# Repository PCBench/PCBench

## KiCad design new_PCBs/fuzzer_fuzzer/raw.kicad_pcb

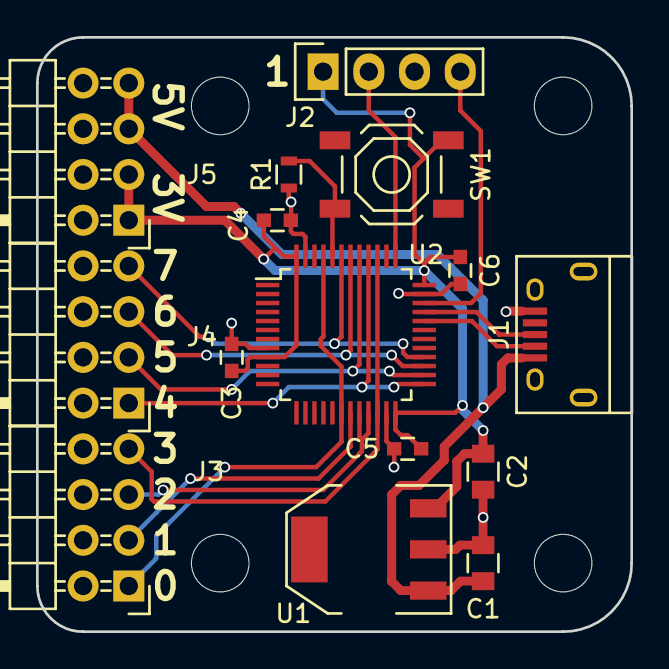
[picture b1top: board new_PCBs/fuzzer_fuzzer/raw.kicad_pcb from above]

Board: 2 copper layers, 33.0 x 33.0 mm, 15 parts (0 on the bottom side), 16 nets.

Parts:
C1, C2: 1u; C_0805
C3, C4, C5, C6: 100n; C_0603
J1: USB_OTG; USB_Micro-B
J2: CONN_01X04; Pin_Header_Straight_1x04
J3, J4, J5: CONN_02X04; Pin_Header_Angled_2x04
R1: 10K; R_0603
SW1: SPST; SW_SPST_TL3342
U1: SOT223-REG; SOT-223
U2: STM32F042-48; LQFP-48_7x7mm_Pitch0.5mm

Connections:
+5V: C1.1, J1.1, J5.5, J5.7, U1.1
/BOOT: R1.1, SW1.1, U2.44
/D0: J3.1, U2.18, U2.45
/D1: J3.3, U2.19
/D2: J3.5, U2.20, U2.21
/D3: J3.7, U2.22, U2.39
/D4: J4.1, U2.25, U2.40
/D5: J4.3, U2.26, U2.41
/D6: J4.5, U2.27, U2.42
/D7: J4.7, U2.28, U2.43
/SWCLK: J2.2, U2.37
/SWDAT: J2.4, U2.34
/USB_DM: J1.2, U2.32
/USB_DP: J1.3, U2.33
GND: C1.2, C2.2, C3.2, C4.2, C5.2, C6.2, J1.5, J2.3, J3.2, J3.4, J3.6, J3.8, J4.2, J4.4, J4.6, J4.8, J5.2, J5.4, J5.6, J5.8, R1.2, U1.2, U1.4, U2.8, U2.23, U2.35, U2.47
VDD: C2.1, C3.1, C4.1, C5.1, C6.1, J2.1, J5.1, J5.3, SW1.2, U1.3, U2.9, U2.24, U2.36, U2.48

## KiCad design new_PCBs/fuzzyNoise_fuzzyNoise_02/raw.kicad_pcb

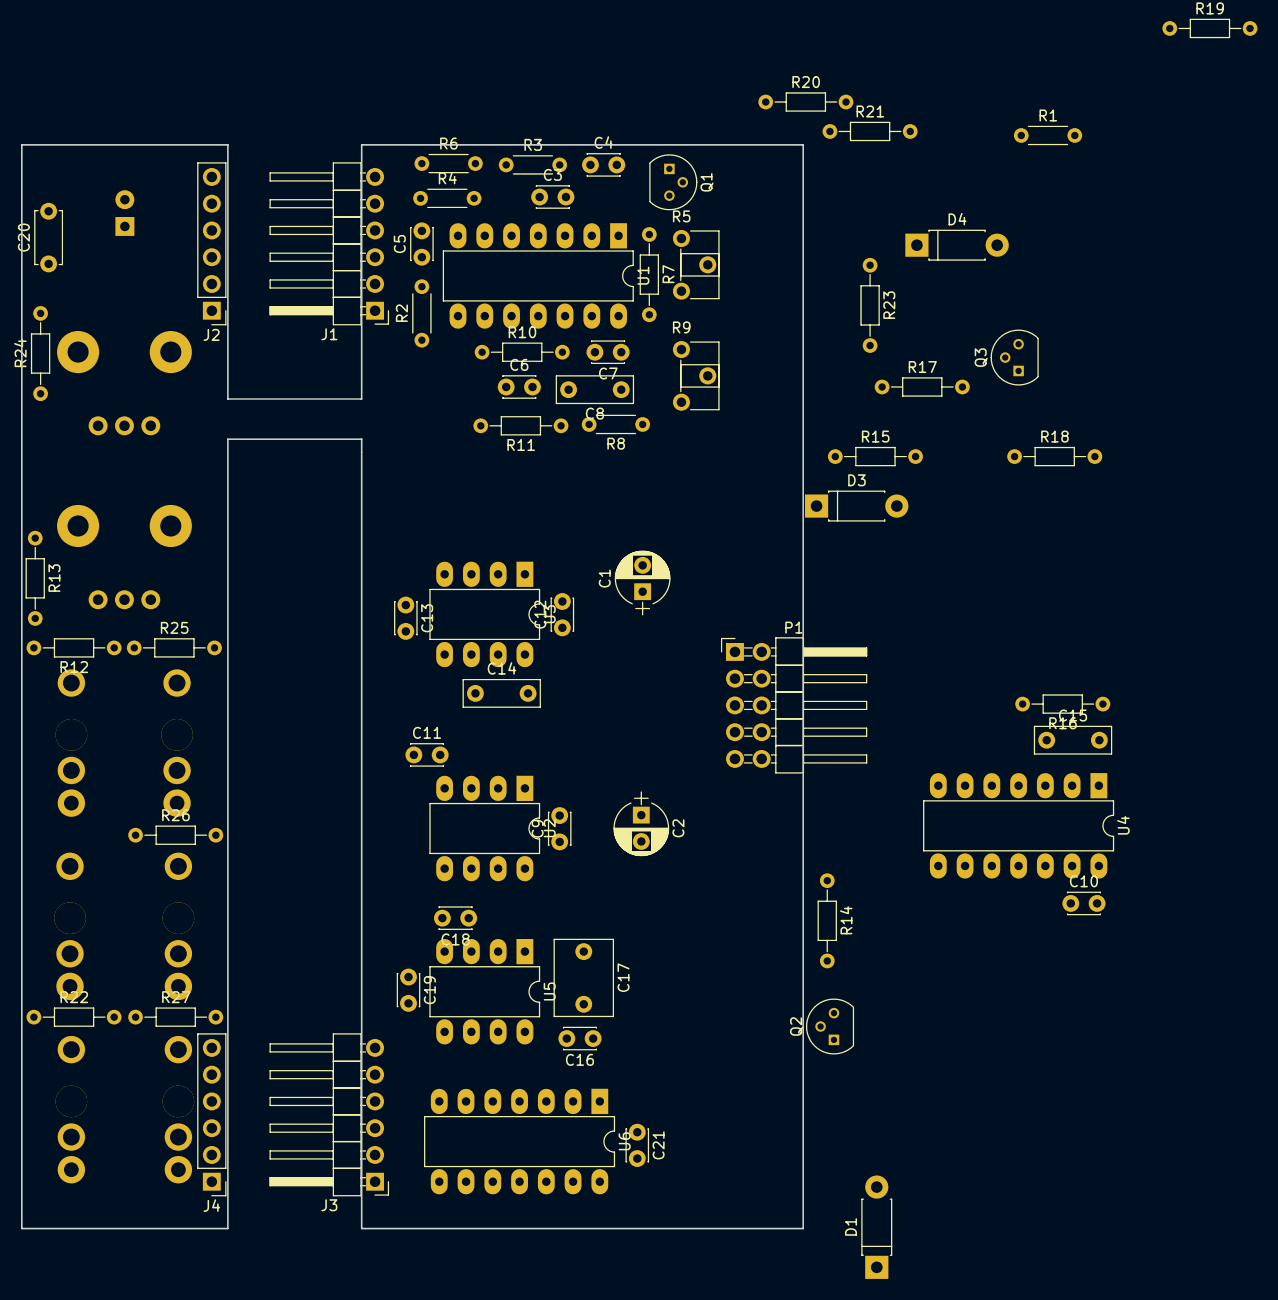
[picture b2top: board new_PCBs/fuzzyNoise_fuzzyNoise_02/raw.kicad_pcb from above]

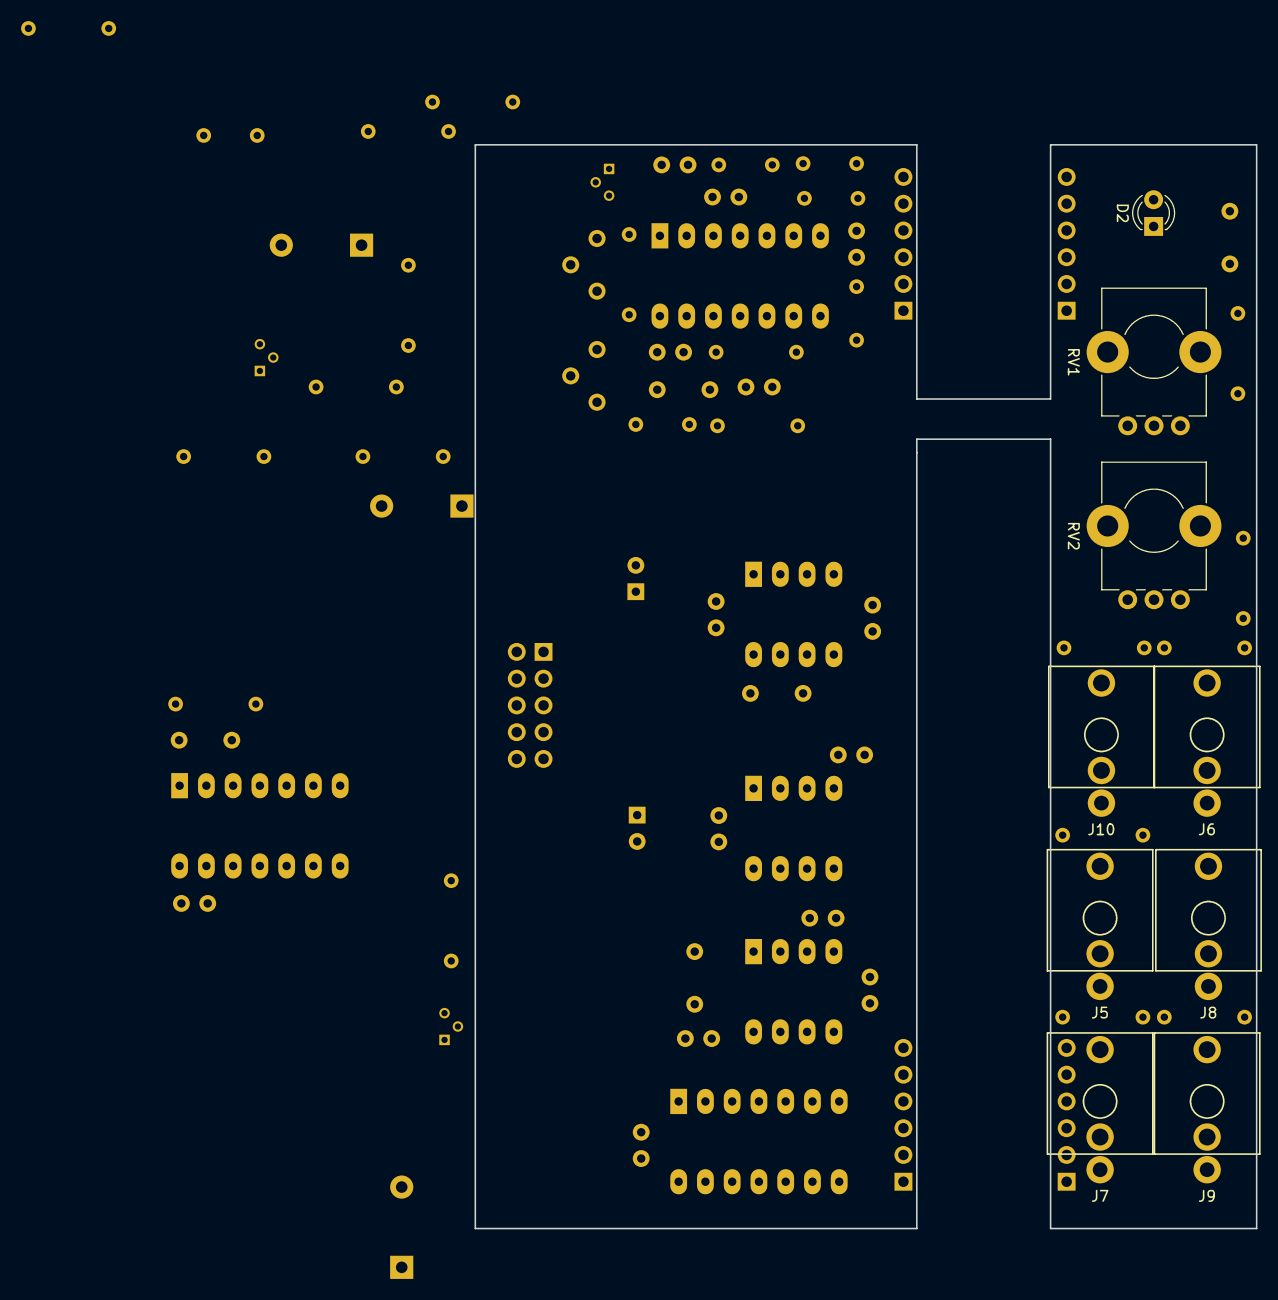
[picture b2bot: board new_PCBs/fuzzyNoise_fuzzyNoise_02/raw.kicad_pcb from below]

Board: 2 copper layers, 74.2 x 102.9 mm, 74 parts (9 on the bottom side), 58 nets, no tracks yet.

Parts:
C1, C2: 10uF; CP_Radial_D5.0mm_P2.50mm
C3, C5, C6, C9, C10, C11, C12, C13, C16, C18, C19, C21: 100nF; C_Disc_D3.0mm_W2.0mm_P2.50mm
C4: 220nF; C_Disc_D3.0mm_W2.0mm_P2.50mm
C7: 1nF; C_Disc_D3.0mm_W2.0mm_P2.50mm
C8: 10nF; C_Rect_L7.2mm_W2.5mm_P5.00mm_FKS2_FKP2_MKS2_MKP2
C14: 2n2 polybox; C_Rect_L7.2mm_W2.5mm_P5.00mm_FKS2_FKP2_MKS2_MKP2
C15: 1nF; C_Rect_L7.2mm_W2.5mm_P5.00mm_FKS2_FKP2_MKS2_MKP2
C17: 1uF; C_Rect_L7.2mm_W5.5mm_P5.00mm_FKS2_FKP2_MKS2_MKP2
C20: 470nF; C_Disc_D5.0mm_W2.5mm_P5.00mm
D1, D3, D4: 1N4148; D_DO-41_SOD81_P7.62mm_Horizontal
D2: LED; LED_D3.0mm
J1: mainTop; Pin_Header_Angled_1x06_Pitch2.54mm
J2: panelTop; Socket_Strip_Straight_1x06_Pitch2.54mm
J3: mainBase; Pin_Header_Angled_1x06_Pitch2.54mm
J4: panelBase; Socket_Strip_Straight_1x06_Pitch2.54mm
J5: whiteOut; Thonkiconn
J6: signalIn; Thonkiconn
J7: pinkOut; Thonkiconn
J8: gateIn; Thonkiconn
J9: LFOout; Thonkiconn
J10: CVout; Thonkiconn
P1: PWR_IN_02x05_conn; Pin_Header_Angled_2x05_Pitch2.54mm
Q1, Q2, Q3: 2N3904; TO-92_Molded_Narrow
R1: 1M; R_Axial_DIN0204_L3.6mm_D1.6mm_P5.08mm_Horizontal
R2, R4, R8: 10K; R_Axial_DIN0204_L3.6mm_D1.6mm_P5.08mm_Horizontal
R3: 2M2; R_Axial_DIN0204_L3.6mm_D1.6mm_P5.08mm_Horizontal
R5: 500K trim; Potentiometer_Trimmer_ACP_CA6h_Vertical
R6: 470K; R_Axial_DIN0204_L3.6mm_D1.6mm_P5.08mm_Horizontal
R7, R13, R18, R19, R20: 100K; R_Axial_DIN0204_L3.6mm_D1.6mm_P7.62mm_Horizontal
R9: 100K trim; Potentiometer_Trimmer_ACP_CA6h_Vertical
R10: 47K; R_Axial_DIN0204_L3.6mm_D1.6mm_P7.62mm_Horizontal
R11: 270K; R_Axial_DIN0204_L3.6mm_D1.6mm_P7.62mm_Horizontal
R12, R22, R24, R25, R26, R27: 1K; R_Axial_DIN0204_L3.6mm_D1.6mm_P7.62mm_Horizontal
R14, R23: 10K; R_Axial_DIN0204_L3.6mm_D1.6mm_P7.62mm_Horizontal
R15: 1M; R_Axial_DIN0204_L3.6mm_D1.6mm_P7.62mm_Horizontal
R16: 1K5; R_Axial_DIN0204_L3.6mm_D1.6mm_P7.62mm_Horizontal
R17: 2K; R_Axial_DIN0204_L3.6mm_D1.6mm_P7.62mm_Horizontal
R21: 22K; R_Axial_DIN0204_L3.6mm_D1.6mm_P7.62mm_Horizontal
RV1: 1M lin; Potentiometer_Alps_RK09K_Horizontal
RV2: 470K lin; Potentiometer_Alps_RK09K_Horizontal
U1, U6: TL074; DIP-14_W7.62mm_LongPads
U2, U5: TL072; DIP-8_W7.62mm_LongPads
U3: LF398; DIP-8_W7.62mm_LongPads
U4: 4047; DIP-14_W7.62mm_LongPads

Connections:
/LFO/CV_out: J3.6, U6.6, U6.7
/LFO/LFO_out: J3.1, U6.1, U6.2
/LFO/from_glide_pot: J1.2, U6.5
/LFO/from_rate_pot: J1.4, R20.1, R21.2, U5.7
/LFO/pinkNoise_out_preBuffer: R9.1, U1.8, U6.12
/LFO/pink_noise_out: J3.2, U6.13, U6.14
/LFO/to_LED: J1.6, Q3.1
/LFO/to_rate_pot: C17.1, J1.5, U5.6
/LFO/whiteNoise_out_preBuffer: R5.1, R7.1, U1.1, U6.10
/LFO/white_noise_out: J3.4, U6.8, U6.9
/panel/CV_out: J4.6, R25.2
/panel/LFO_out: J4.1, R22.2
/panel/from_glide_pot: C20.1, J2.2, RV2.1
/panel/from_rate_pot: J2.4, RV1.1, RV1.2
/panel/gate_input: J4.3, J8.3
/panel/ground: C20.2, D2.1, J2.1, J5.1, J6.1, J7.1, J8.1, J9.1, J10.1, R13.2
/panel/pink_noise_out: J4.2, R27.2
/panel/signal_in: J4.5, R12.1, R13.1
/panel/to_LED: D2.2, J2.6
/panel/to_glide_pot: J2.3, RV2.2, RV2.3
/panel/to_rate_pot: J2.5, R24.2
/panel/white_noise_out: J4.4, R26.2
/sampleAndHold/gate_input: D1.1, J3.3, Q2.2, R15.1
/sampleAndHold/signal_in: J3.5, U2.3
/sampleAndHold/to_glide_pot: J1.3, U2.6, U2.7
GND: C1.2, C2.1, C3.2, C6.1, C9.1, C10.1, C11.1, C12.1, C13.2, C14.2, C16.1, C17.2, C18.1, C19.1, C21.1, D1.2, J1.1, P1.3, P1.4, P1.5, P1.6, P1.7, P1.8, Q2.1, R3.2, R4.2, R15.2, R19.2, U1.3, U1.10, U1.12, U3.7, U4.5, U4.7, U4.9, U4.12, U5.3
unnamed: C4.1, R3.1, U1.5
unnamed: C4.2, Q1.1, R1.2
unnamed: C5.1, R2.2
unnamed: C5.2, R6.1, U1.7
unnamed: C7.1, C8.1, R8.2, R11.1, U1.14
unnamed: C7.2, R7.2, R10.2, R11.2, U1.13
unnamed: C8.2, R10.1
unnamed: C14.1, U3.6
unnamed: C15.1, R16.2, U4.3
unnamed: C15.2, U4.1
unnamed: D3.1, R18.2, R23.1, U6.3
unnamed: D3.2, D4.1, U5.1
unnamed: D4.2, R21.1, R23.2, U5.2
unnamed: J5.3, J6.2, R26.1
unnamed: J6.3, R12.2
unnamed: J7.3, R27.1
unnamed: J8.2, J9.3, R22.1
unnamed: J10.3, R25.1
unnamed: Q2.3, R14.2, U4.6
unnamed: Q3.2, R18.1
unnamed: Q3.3, R17.1
unnamed: R2.1, R5.2, U1.2
unnamed: R4.1, R6.2, U1.6
unnamed: R8.1, R9.2, U1.9
unnamed: R16.1, U4.2
unnamed: R19.1, R20.2, U5.5
unnamed: R24.1, RV1.3
unnamed: U2.1, U2.2, U3.3
unnamed: U2.5, U3.5
unnamed: U3.8, U4.10
VCC: C1.1, C3.1, C9.2, C10.2, C12.2, C16.2, C19.2, P1.1, P1.2, R1.1, R14.1, R17.2, U1.4, U2.8, U3.1, U4.4, U4.8, U4.14, U5.8, U6.4
VEE: C2.2, C6.2, C11.2, C13.1, C18.2, C21.2, P1.9, P1.10, Q1.2, U1.11, U2.4, U3.4, U5.4, U6.11

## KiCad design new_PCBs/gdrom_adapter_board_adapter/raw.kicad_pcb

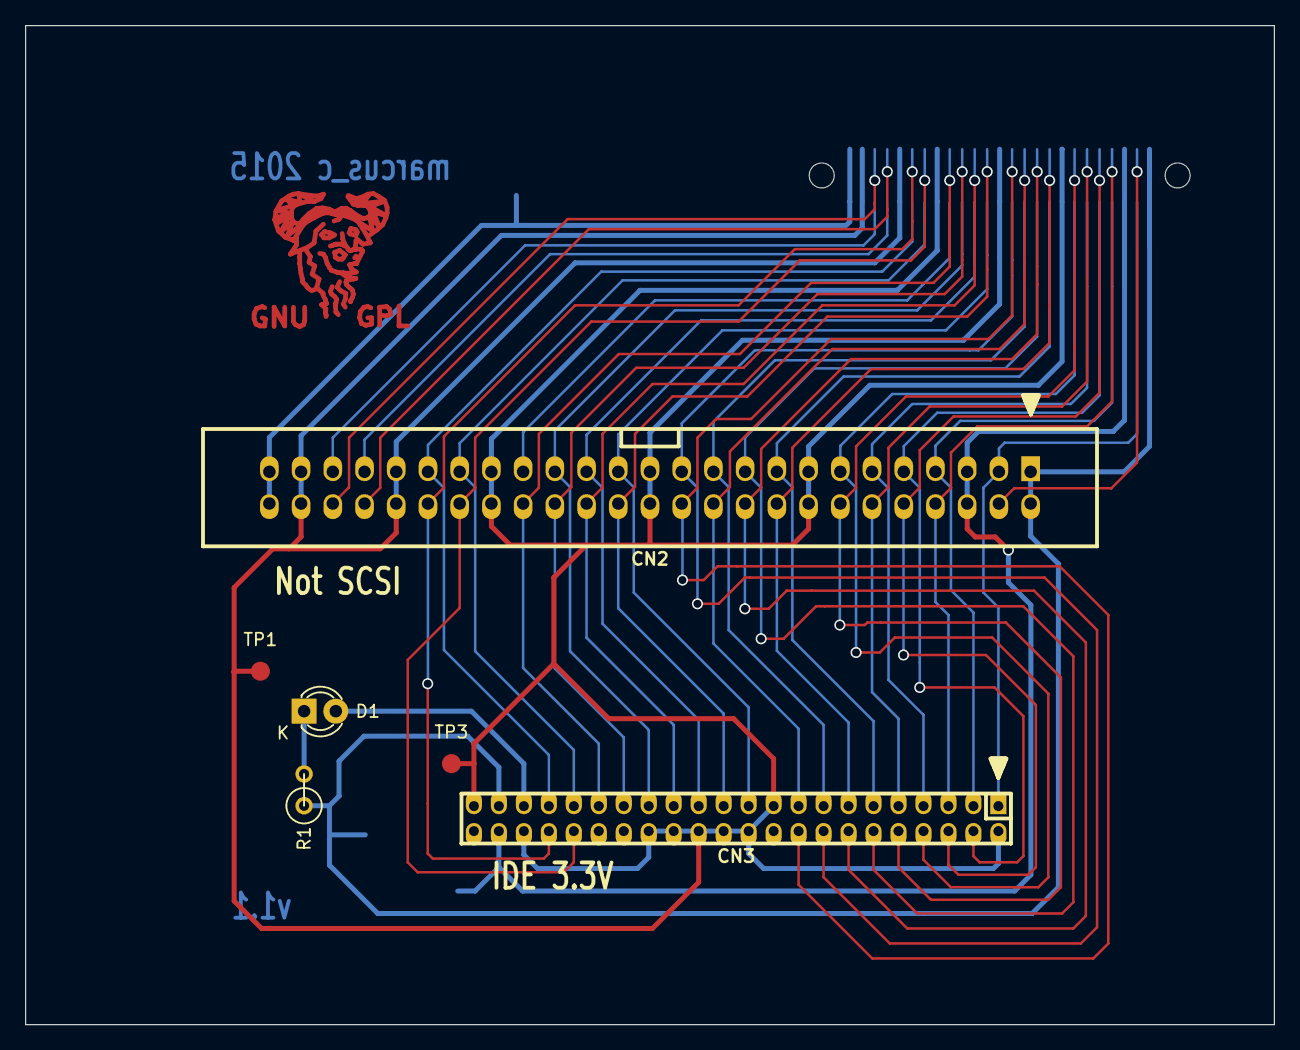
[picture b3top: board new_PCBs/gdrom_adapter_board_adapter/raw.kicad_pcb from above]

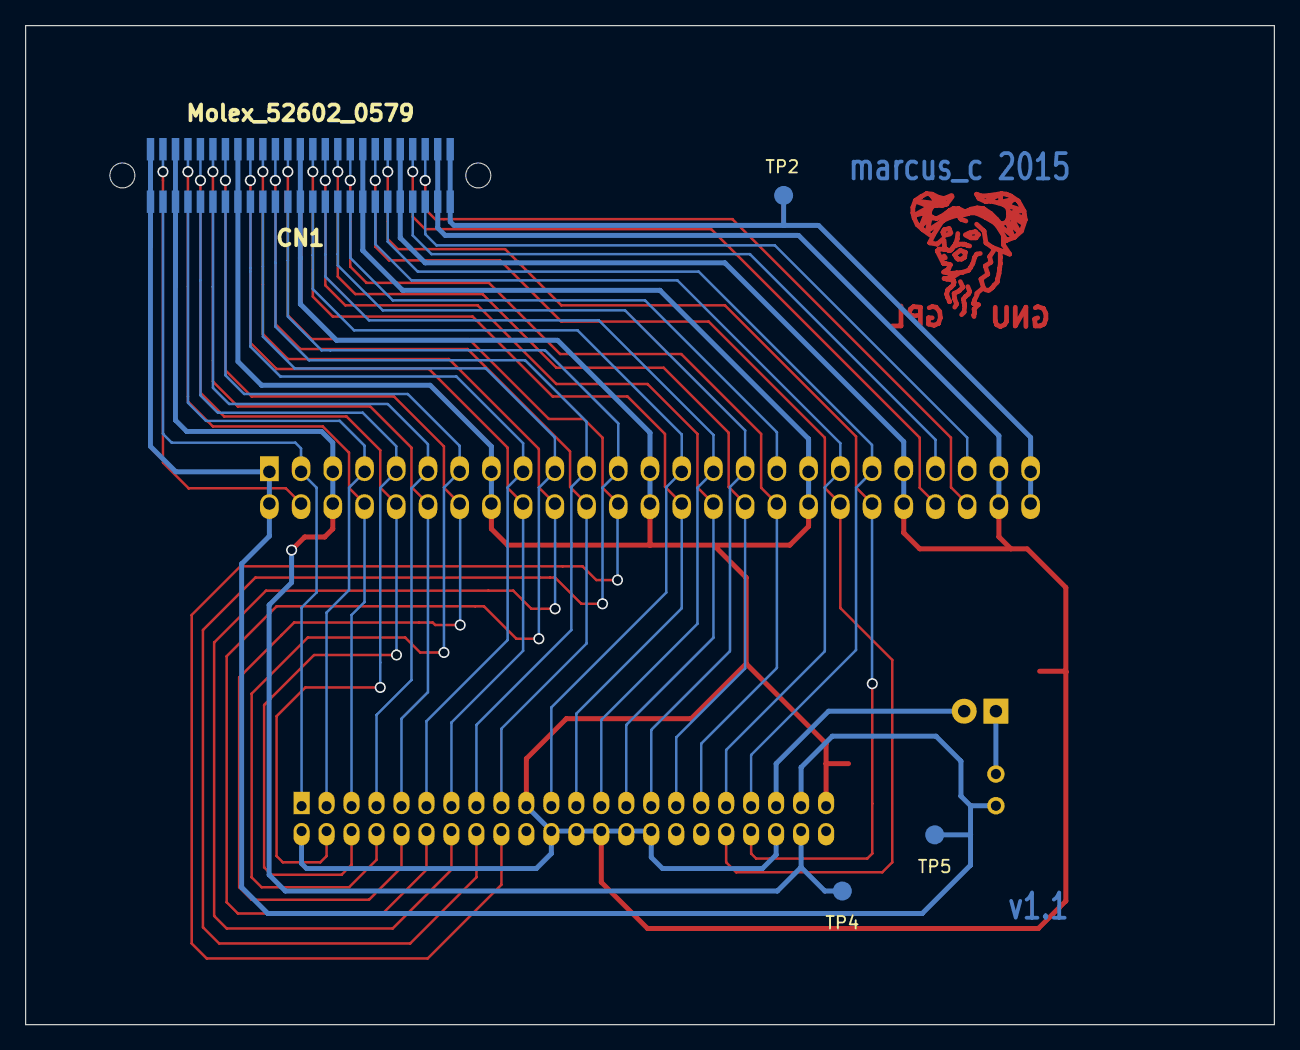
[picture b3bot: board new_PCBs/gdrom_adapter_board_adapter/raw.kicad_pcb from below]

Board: 2 copper layers, 100.0 x 80.0 mm, 10 parts (4 on the bottom side), 40 nets.

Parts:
CN1: Molex_52602_0579
CN2: CONN_25X2; vasch_strip_25x2
CN3: CONN_02X22; pin_strip_2mm_22x2
D1: LED; LED-3MM
R1: 1k; R1
TP1, TP2, TP3, TP4, TP5: Measurement_Point_Round-SMD-Pad_Small

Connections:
+3V3: CN1.A1, CN1.B1, CN2.1, CN2.2, CN3.41, R1.1, TP5.1
+5V: CN1.A3, CN1.B3, CN2.5, CN2.6, CN3.42, TP4.1
+12V: CN1.A25, CN1.B25, CN2.49, CN2.50, TP2.1
/A0: CN1.A19, CN2.37, CN3.35
/A1: CN1.B17, CN2.34, CN3.33
/A2: CN1.B19, CN2.38, CN3.36
/ACTIVEn: CN3.39, D1.2
/CD_CLK: CN1.B23, CN2.46
/CS0n: CN1.A20, CN2.39, CN3.37
/CS1n: CN1.B20, CN2.40, CN3.38
/D0: CN1.B11, CN2.22, CN3.17
/D1: CN1.A11, CN2.21, CN3.15
/D2: CN1.B9, CN2.18, CN3.13
/D3: CN1.A9, CN2.17, CN3.11
/D4: CN1.B6, CN2.12, CN3.9
/D5: CN1.A6, CN2.11, CN3.7
/D6: CN1.B4, CN2.8, CN3.5
/D7: CN1.A4, CN2.7, CN3.3
/D8: CN1.A5, CN2.9, CN3.4
/D9: CN1.B5, CN2.10, CN3.6
/D10: CN1.A7, CN2.13, CN3.8
/D11: CN1.B7, CN2.14, CN3.10
/D12: CN1.A10, CN2.19, CN3.12
/D13: CN1.B10, CN2.20, CN3.14
/D14: CN1.A12, CN2.23, CN3.16
/D15: CN1.B12, CN2.24, CN3.18
/DMACKn: CN1.A16, CN2.31, CN3.29
/DMARQ: CN1.A14, CN2.27, CN3.21
/EMPH: CN1.A17, CN2.33
/G_RST: CN1.A2, CN2.3, CN3.1
/INTRQ: CN1.B16, CN2.32, CN3.31
/IORDY: CN1.B15, CN2.30, CN3.27
/LRCK: CN1.B22, CN2.44
/RDn: CN1.A15, CN2.29, CN3.25
/SCK: CN1.A22, CN2.43
/SDAT: CN1.A23, CN2.45
/WRn: CN1.B14, CN2.28, CN3.23
/xB2: CN1.B2, CN2.4
GND: CN1.A8, CN1.A13, CN1.A18, CN1.A21, CN1.A24, CN1.B8, CN1.B13, CN1.B18, CN1.B21, CN1.B24, CN2.15, CN2.16, CN2.25, CN2.26, CN2.35, CN2.36, CN2.41, CN2.42, CN2.47, CN2.48, CN3.2, CN3.19, CN3.22, CN3.24, CN3.26, CN3.28, CN3.30, CN3.40, CN3.43, TP1.1, TP3.1
unnamed: D1.1, R1.2

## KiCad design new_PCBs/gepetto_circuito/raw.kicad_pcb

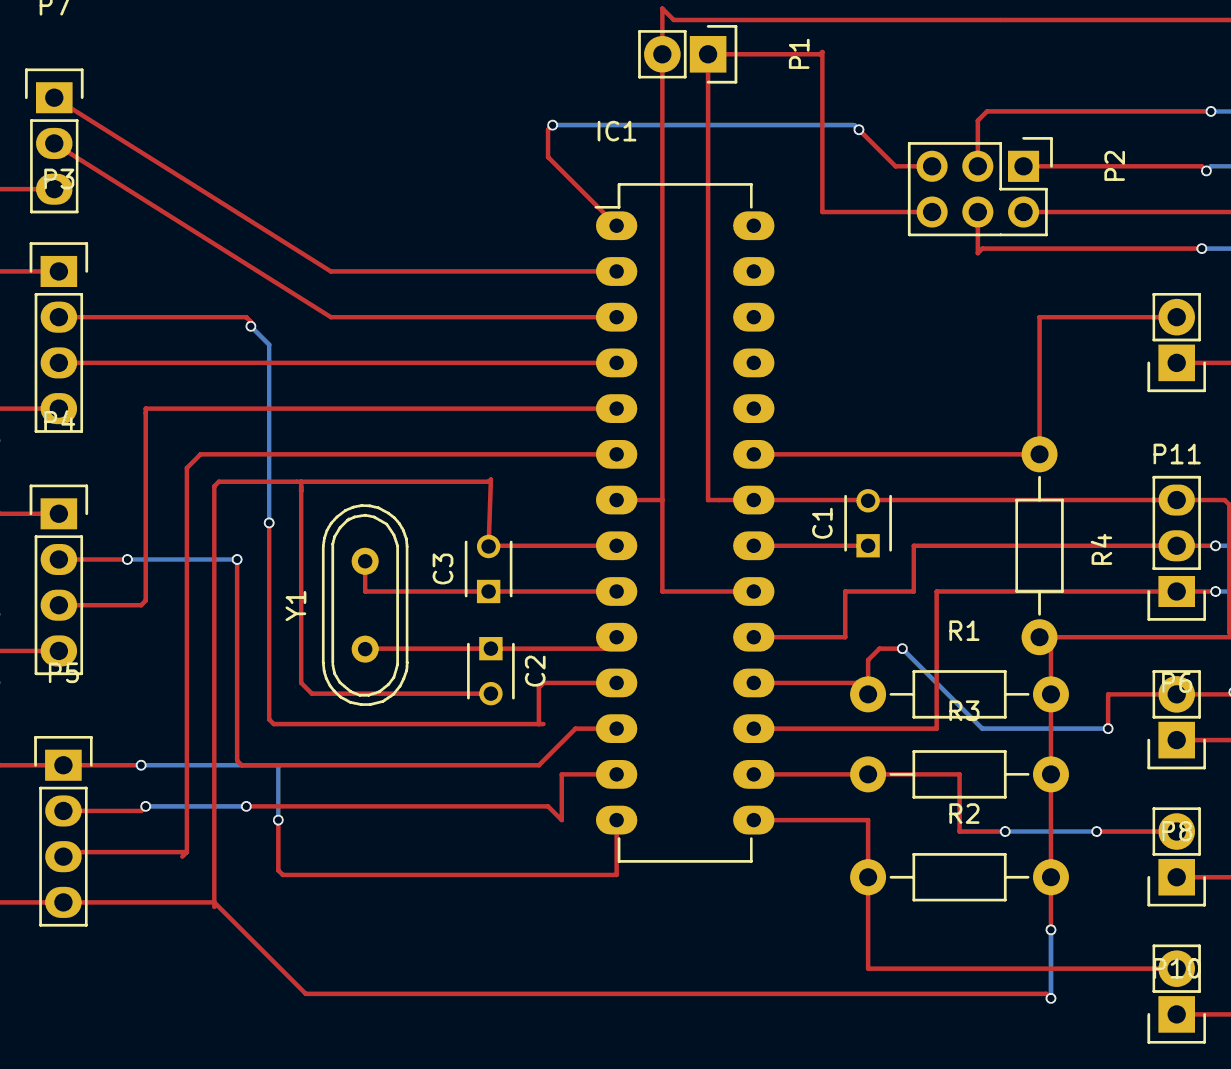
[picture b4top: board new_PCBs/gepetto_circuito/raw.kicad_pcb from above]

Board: 2 copper layers, 20 parts (0 on the bottom side), 21 nets.

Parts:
C1: 100n; C_Disc_D3_P2.5
C2, C3: 22 pF; C_Disc_D3_P2.5
IC1: ATMEGA328-P; DIP-28_W7.62mm_LongPads
P1: CONN_5V; Pin_Header_Straight_1x02
P2: CONN_02X03; Pin_Header_Straight_2x03
P3: CONN_EJE_X; Pin_Header_Straight_1x04
P4: CONN_EJE_Y; Pin_Header_Straight_1x04
P5: CONN_EJE_Z; Pin_Header_Straight_1x04
P6: CONN_HUS; Pin_Header_Straight_1x03
P7: CONN_UART; Pin_Header_Straight_1x03
P8: CONN_LIM_Z; Pin_Header_Straight_1x02
P9: CONN_LIM_X; Pin_Header_Straight_1x02
P10: CONN_LIM_Y; Pin_Header_Straight_1x02
P11: CONN_E_STOP; Pin_Header_Straight_1x02
R1, R2, R3, R4: 15 k; Resistor_Horizontal_RM10mm
Y1: 16Mhz; Crystal_HC49-U_Vertical

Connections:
/MISO: IC1.18, P2.1, P8.2, R1.1
/MOSI: IC1.17, P2.4, P6.1
/RESET: IC1.1, P2.5
/Rx_int: IC1.2, P7.1
/SCK: IC1.19, P2.3, P6.2
/Tx_int: IC1.3, P7.2
/button_stop: IC1.23, P11.2, R4.1
/dir_X: IC1.11, P3.2
/dir_Y: IC1.12, P4.2
/dir_Z: IC1.13, P5.2
/enable: IC1.14, P3.1, P4.1, P5.1
/lim_X: IC1.15, P9.2, R2.1
/lim_Y: IC1.16, P10.2, R3.1
/step_X: IC1.4, P3.3
/step_Y: IC1.5, P4.3
/step_Z: IC1.6, P5.3
GND: C1.2, C2.2, C3.2, IC1.8, IC1.22, P1.1, P2.6, P3.4, P4.4, P5.4, P6.3, P7.3, R1.2, R2.2, R3.2, R4.2
unnamed: C1.1, IC1.21
unnamed: C2.1, IC1.10, Y1.1
unnamed: C3.1, IC1.9, Y1.2
VCC: IC1.7, IC1.20, P1.2, P2.2, P8.1, P9.1, P10.1, P11.1

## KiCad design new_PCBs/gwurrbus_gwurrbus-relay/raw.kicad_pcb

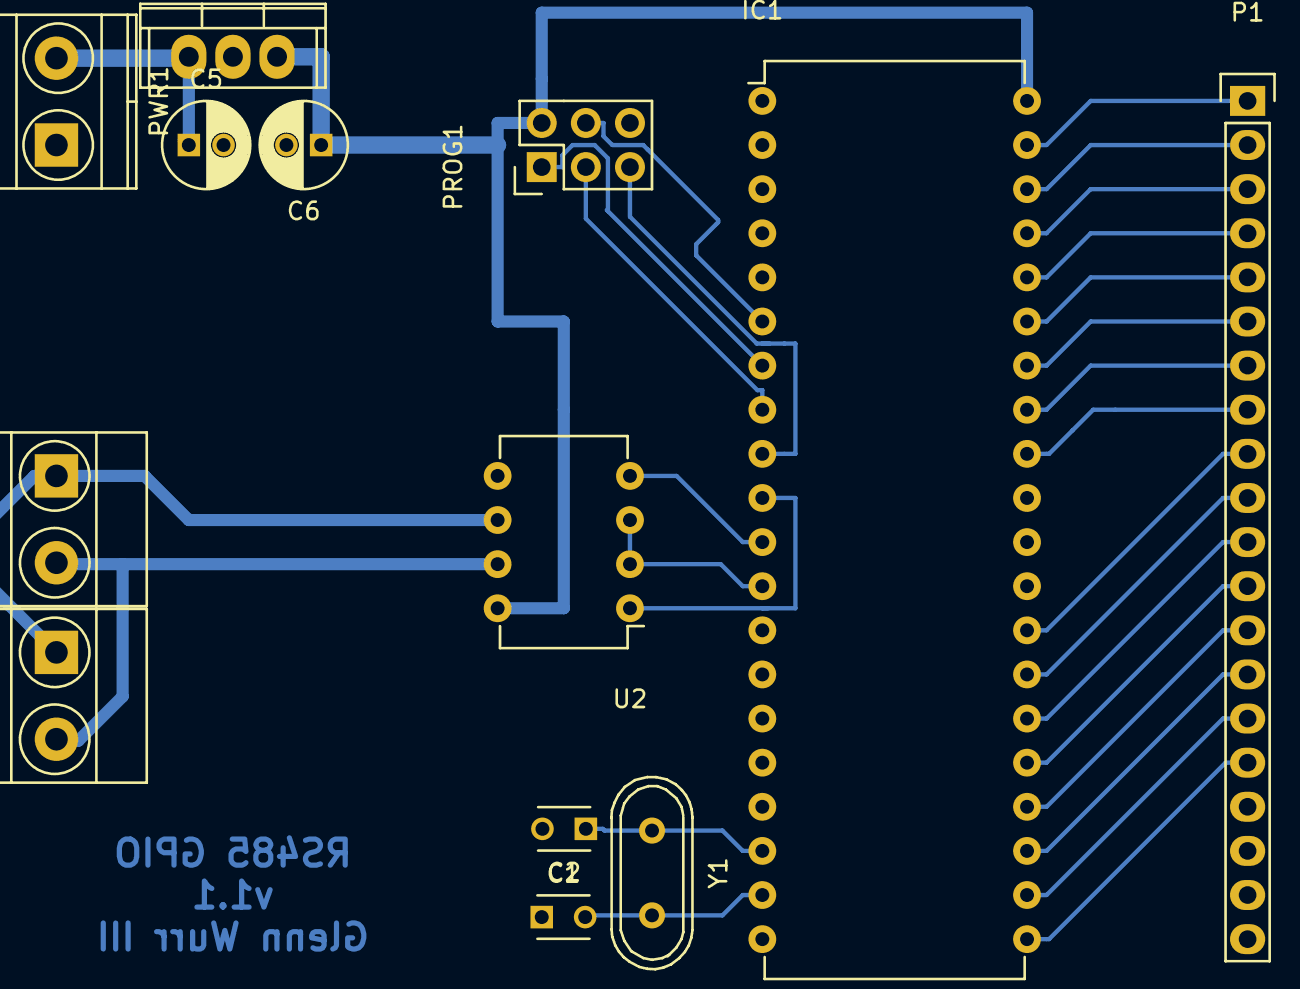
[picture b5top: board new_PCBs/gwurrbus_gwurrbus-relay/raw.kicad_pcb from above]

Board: 2 copper layers, 13 parts (0 on the bottom side), 30 nets.

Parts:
C1, C2: C_Small; C_Disc_D3_P2.5
C5, C6: 10uf; C_Radial_D5_L11_P2
IC1: AT90S8515-P; DIP-40_W15.24mm
P1: CONN_01X20; Pin_Header_Straight_1x20
PROG1: CONN_02X03; Pin_Header_Straight_2x03
PWR1: CONN_01X02; TerminalBlock_Pheonix_MKDS1.5-2pol
RS485, RS485S1: CONN_01X02; TerminalBlock_Pheonix_MKDS1.5-2pol
U1: LM7805CT; TO-220
U2: SP3485CP; DIP-8_W7.62mm
Y1: 16mhz; Crystal_HC49-U_Vertical

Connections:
+5V: C6.1, IC1.40, PROG1.2, U1.3, U2.8
+BATT: C5.1, PWR1.2, U1.1
/MISO: IC1.7, PROG1.1
/MOSI: IC1.6, PROG1.4
/O1: IC1.39, P1.1
/O2: IC1.38, P1.2
/O3: IC1.37, P1.3
/O4: IC1.36, P1.4
/O5: IC1.35, P1.5
/O6: IC1.34, P1.6
/O7: IC1.33, P1.7
/O8: IC1.32, P1.8
/O9: IC1.21, P1.16
/O10: IC1.22, P1.15
/O11: IC1.23, P1.14
/O12: IC1.24, P1.13
/O13: IC1.25, P1.12
/O14: IC1.26, P1.11
/O15: IC1.27, P1.10
/O16: IC1.28, P1.9
/RESET: IC1.9, PROG1.5
/SCK: IC1.8, PROG1.3
Earth: C1.1, C2.2, C5.2, C6.2, IC1.20, P1.17, P1.18, P1.19, P1.20, PROG1.6, PWR1.1, U1.2, U2.5
unnamed: C1.2, IC1.19, Y1.2
unnamed: C2.1, IC1.18, Y1.1
unnamed: IC1.10, U2.1
unnamed: IC1.11, U2.4
unnamed: IC1.12, U2.2, U2.3
unnamed: RS485.1, RS485S1.1, U2.6
unnamed: RS485.2, RS485S1.2, U2.7

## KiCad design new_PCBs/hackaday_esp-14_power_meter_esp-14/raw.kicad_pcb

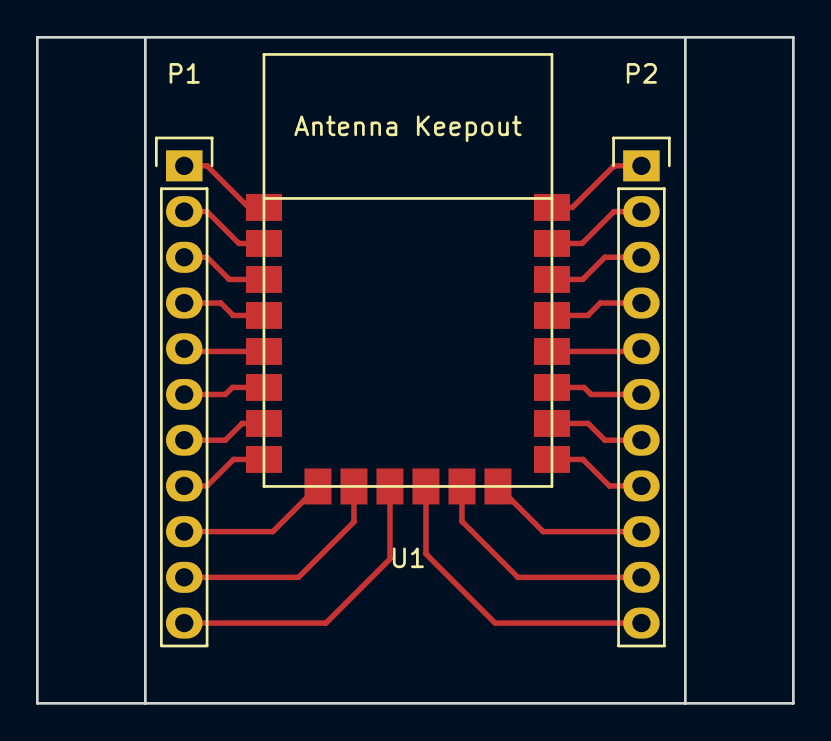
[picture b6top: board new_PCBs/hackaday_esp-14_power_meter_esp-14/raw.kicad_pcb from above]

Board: 2 copper layers, 42.0 x 37.0 mm, 3 parts (0 on the bottom side), 22 nets.

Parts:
P1, P2: CONN_01X11; Pin_Header_Straight_1x11
U1: esp-14

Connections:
unnamed: P1.1, U1.1
unnamed: P1.2, U1.2
unnamed: P1.3, U1.3
unnamed: P1.4, U1.4
unnamed: P1.5, U1.5
unnamed: P1.6, U1.6
unnamed: P1.7, U1.7
unnamed: P1.8, U1.8
unnamed: P1.9, U1.9
unnamed: P1.10, U1.10
unnamed: P1.11, U1.11
unnamed: P2.1, U1.22
unnamed: P2.2, U1.21
unnamed: P2.3, U1.20
unnamed: P2.4, U1.19
unnamed: P2.5, U1.18
unnamed: P2.6, U1.17
unnamed: P2.7, U1.16
unnamed: P2.8, U1.15
unnamed: P2.9, U1.14
unnamed: P2.10, U1.13
unnamed: P2.11, U1.12

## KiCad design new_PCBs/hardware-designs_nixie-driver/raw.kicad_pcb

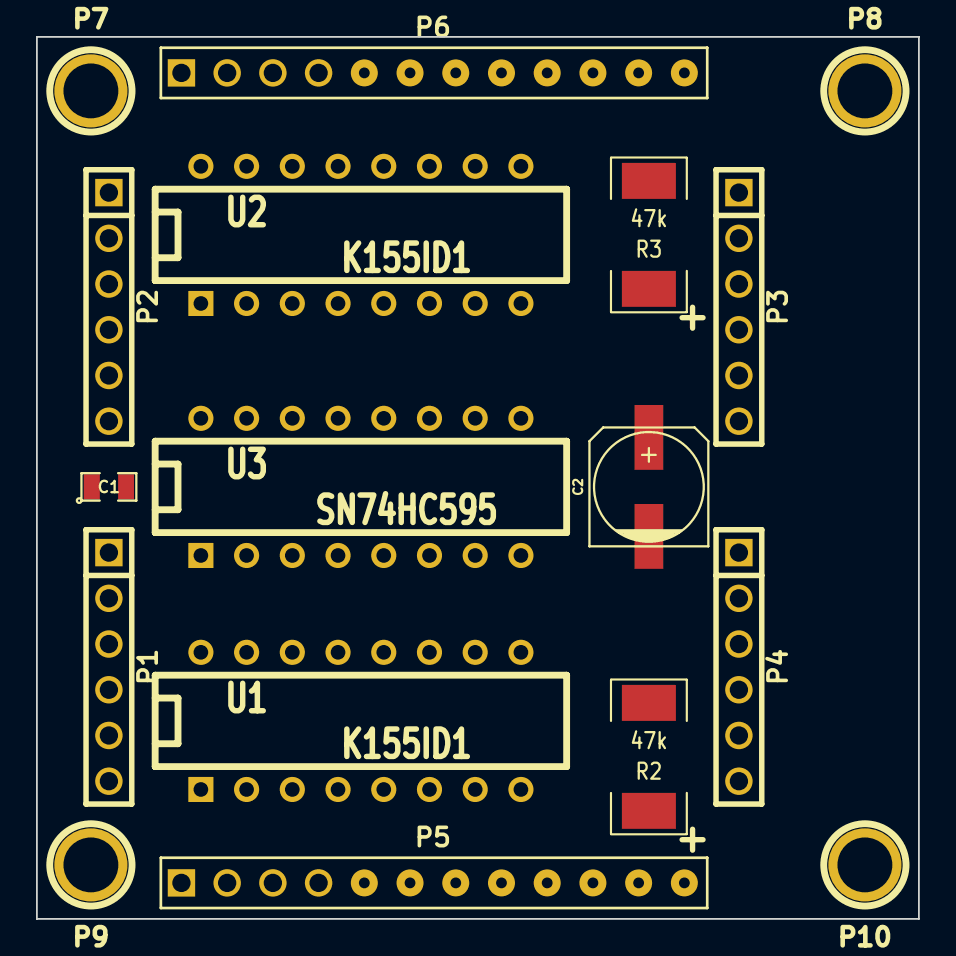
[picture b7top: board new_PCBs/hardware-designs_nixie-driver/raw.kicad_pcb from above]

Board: 2 copper layers, 49.0 x 49.0 mm, 17 parts (0 on the bottom side), 37 nets, no tracks yet.

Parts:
C1: 0.1uF; SM0805
C2: 100uF; c_elec_6.3x7.7
P1, P2, P3, P4: CONN_6; PIN_ARRAY-6X1
P5, P6: CONN_12; PIN_ARRAY_12x1
P7, P8, P9, P10: CONN_1; 1pin
R2, R3: 47k; SM2512
U1, U2: K155ID1; DIP-16__300
U3: SN74HC595; DIP-16__300

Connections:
+3.3V: C1.1, C2.1, P2.5, P3.5, U1.5, U2.5, U3.10, U3.16
GND: C1.2, C2.2, P1.1, P1.2, P1.5, P1.6, P2.2, P3.2, P4.1, P4.2, P4.5, P4.6, P5.12, P6.5, U1.12, U2.12, U3.8, U3.13
HT: P1.3, P1.4, P4.3, P4.4, R2.1, R3.2
unnamed: P6.9, U2.1
unnamed: P6.8, U2.9
unnamed: P6.7, U2.10
unnamed: P6.6, U2.11
unnamed: P6.11, U2.8
unnamed: P6.10, U2.2
unnamed: P5.10, U1.2
unnamed: P5.9, U1.1
unnamed: P5.11, U1.8
unnamed: P6.4, U2.13
unnamed: P6.3, U2.14
unnamed: P6.2, U2.15
unnamed: P6.1, U2.16
unnamed: P5.1, R2.2
unnamed: P6.12, R3.1
unnamed: U1.4, U3.3
unnamed: U2.4, U3.7
unnamed: P5.8, U1.9
unnamed: P2.1, U3.14
unnamed: P3.1, U3.9
unnamed: U1.3, U3.15
unnamed: U1.7, U3.2
unnamed: U1.6, U3.1
unnamed: U2.6, U3.5
unnamed: U2.3, U3.4
unnamed: P5.4, U1.14
unnamed: P5.5, U1.13
unnamed: U2.7, U3.6
unnamed: P5.7, U1.10
unnamed: P5.6, U1.11
unnamed: P5.3, U1.15
unnamed: P5.2, U1.16
unnamed: P2.4, P3.4, U3.12
unnamed: P2.3, P3.3, U3.11
